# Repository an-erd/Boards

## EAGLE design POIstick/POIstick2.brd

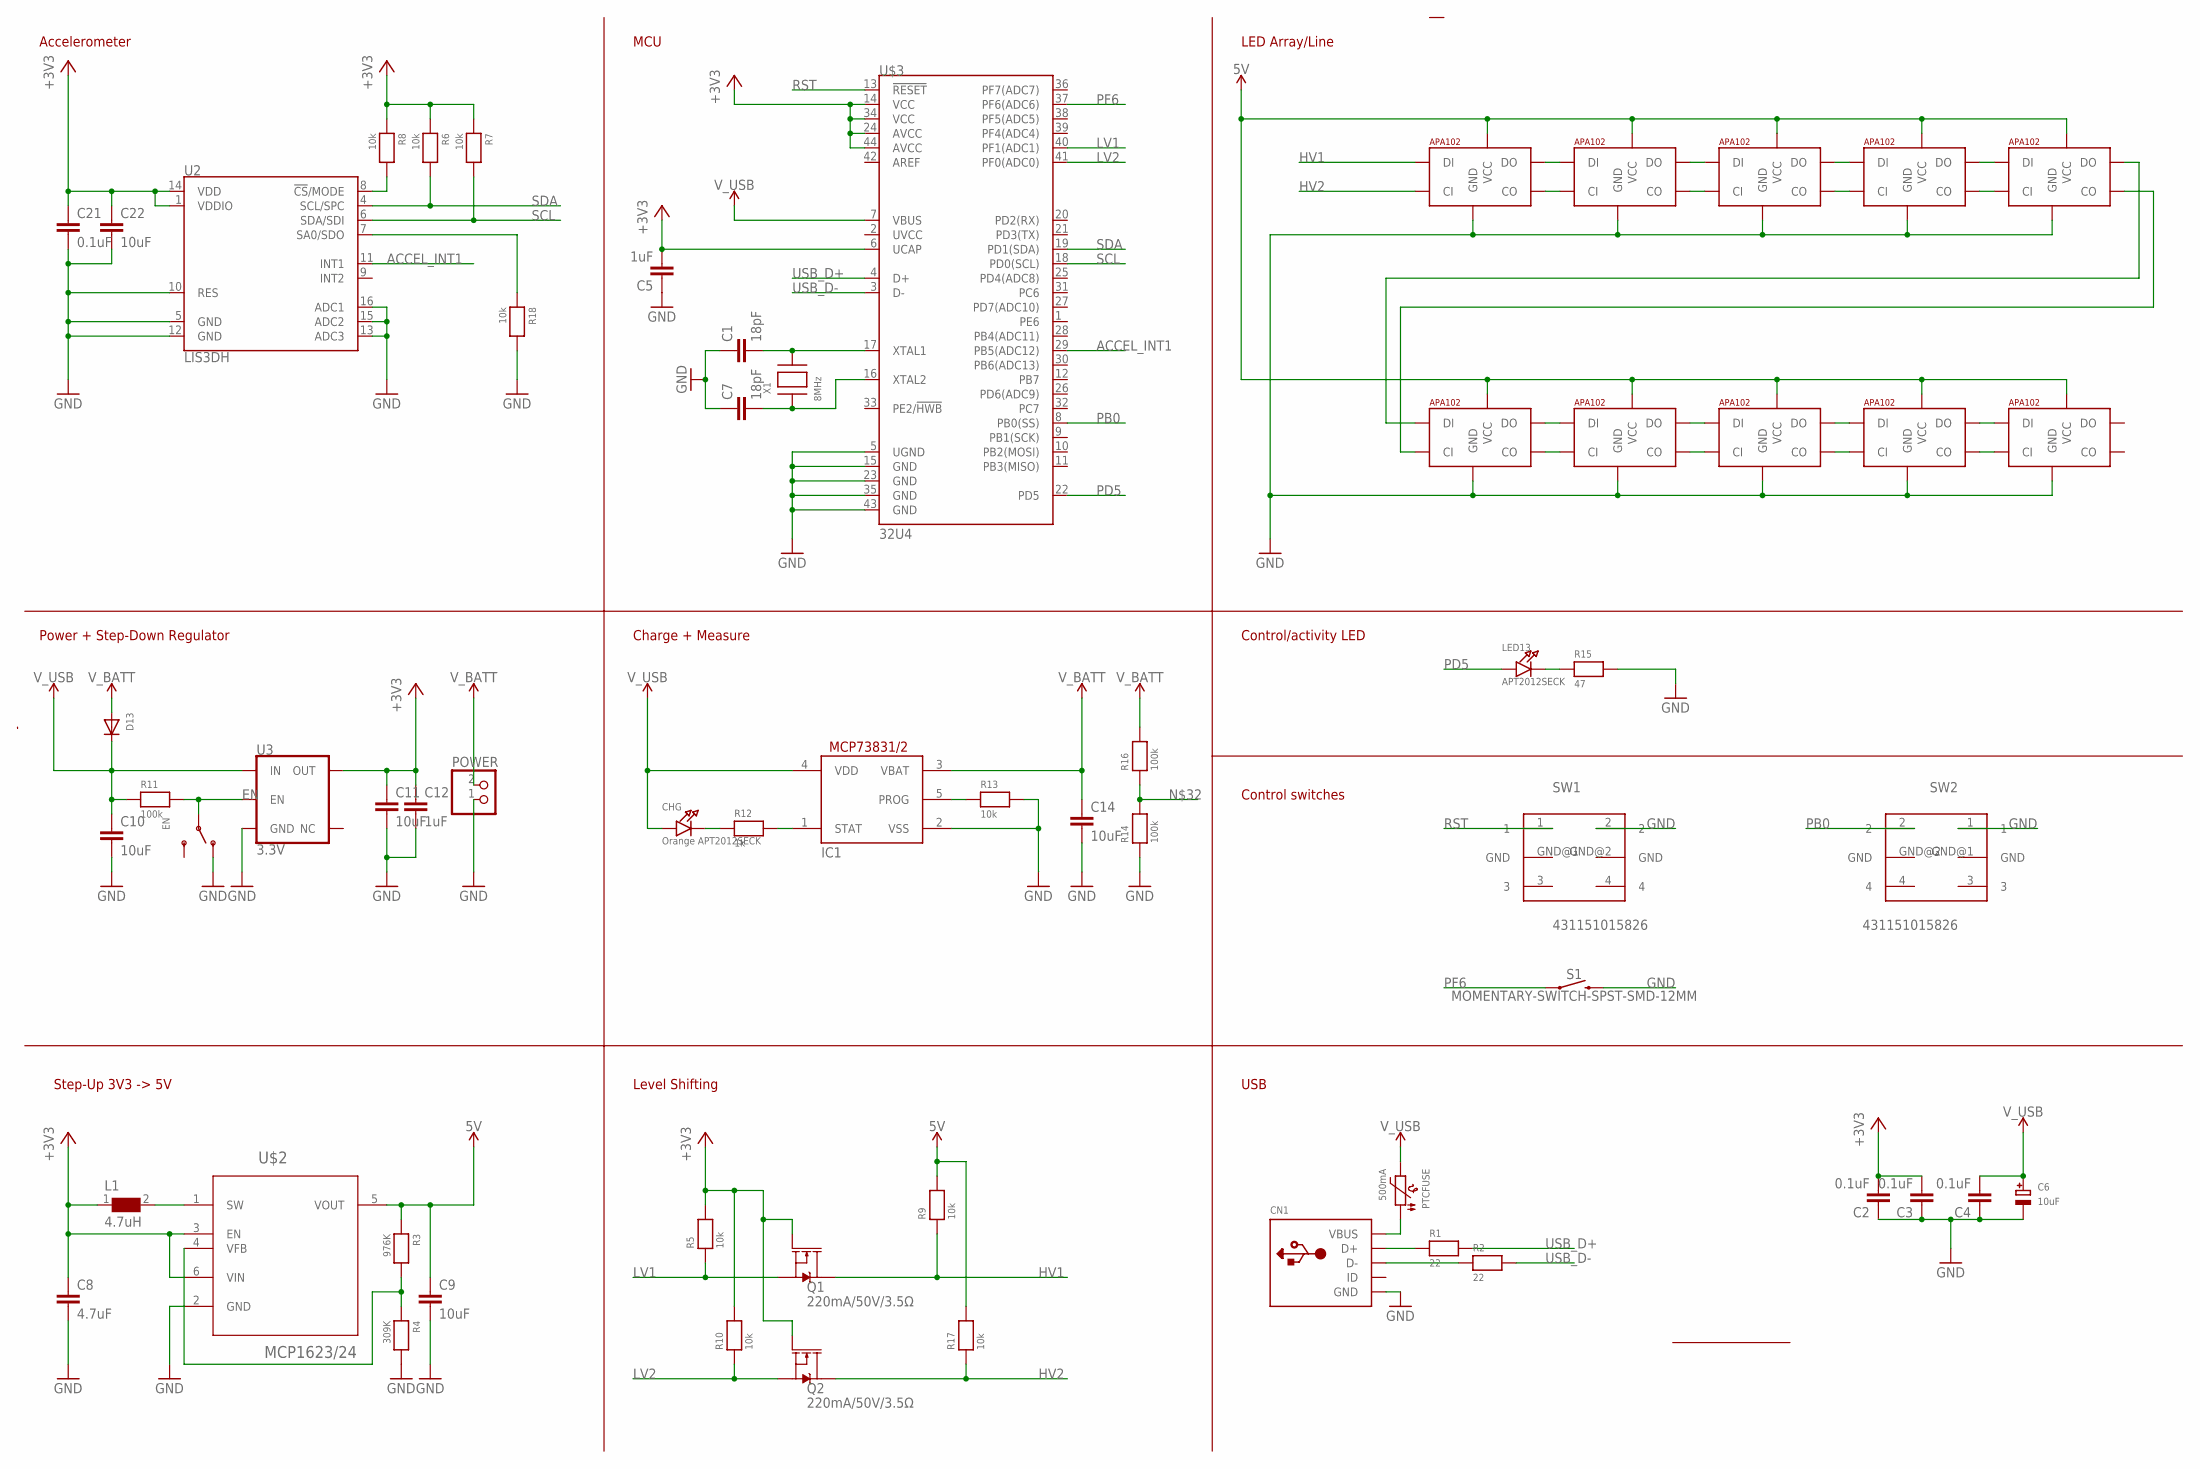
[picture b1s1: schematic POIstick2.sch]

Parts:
C1, C7: 18pF; C0603K
C2, C3, C4, C21: 0.1uF; C0603K
C5, C12: 1uF; C0603K
C6: 10uF; EIA3216-18/A-R
C8: 4.7uF; C0603K
C9, C10, C11, C14, C22: 10uF; C0603K
CHG: Orange APT2012SECK; CHIPLED_0603
CN1: USBMINIB; USB-MINIB
D13: DIODESOD-123; SOD-123
EN: SWITCH_SPDT; SPDT_SMT_SSSS811101
IC1: MCP73831/OT; SOT23-5L
L1: 4.7uH; WE-TPC_3816
LED13: APT2012SECK; CHIPLED_0603
POWER: JST_2PIN-THM; JST-PH-2-THM
PTCFUSE: 500mA; 1206
Q1, Q2: 220mA/50V/3.5Ω; SOT23-3
R1, R2: 22; 0603
R3: 976K; 0603
R4: 309K; 0603
R5, R6, R7, R8, R9, R10, R13, R17, R18: 10k; 0603
R11, R14, R16: 100k; 0603
R12: 1k; 0603
R15: 47; 0603
S1: MOMENTARY-SWITCH-SPST-SMD-12MM; TACTILE_SWITCH_SMD_12MM
SW1, SW2: 431151015826; 431181015816
U2: LIS3DH; LGA-16-3X3
U3: 3.3V; SOT23-5
U$2: MCP1623/24; SOT95P300X120-6N
U$3: 32U4; QFN-44
U$4, U$5, U$6, U$7, U$8, U$9, U$10, U$11, U$12, U$13: APA1025050; APA102_5050
X1: 8MHz; NX5032

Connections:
5V: C9.1, R3.1, R9.2, R17.2, U$2.5 (VOUT), U$4.1 (VCC), U$5.1 (VCC), U$6.1 (VCC), U$7.1 (VCC), U$8.1 (VCC), U$9.1 (VCC), U$10.1 (VCC), U$11.1 (VCC), U$12.1 (VCC), U$13.1 (VCC)
+3V3: C2.2, C3.2, C5.2, C8.1, C11.1, C12.1, C21.1, C22.1, L1.1, Q1.1 (G), Q2.1 (G), R5.2, R6.1, R7.1, R8.1, R10.2, U2.1 (VDDIO), U2.14 (VDD), U3.5 (OUT), U$2.3 (EN), U$2.6 (VIN), U$3.24 (AVCC), U$3.44 (AVCC)
ACCEL_INT1: U2.11 (INT1), U$3.29 (PB5(ADC12))
EN: EN.B, R11.2, U3.3 (EN)
GND: C1.1, C2.1, C3.1, C4.1, C5.1, C6.-, C7.1, C8.2, C9.2, C10.2, C11.2, C12.2, C14.2, C21.2, C22.2, CN1.GND, EN.A (O), IC1.2 (VSS), POWER.1 (2), R4.2, R13.2, R14.1, R15.2, R18.2, S1.3 (2), SW1.2, SW2.1, U2.5 (GND), U2.10 (RES), U2.12 (GND), U2.13 (ADC3), U2.15 (ADC2), U2.16 (ADC1), U3.2 (GND), U$2.2 (GND), U$4.6 (GND), U$5.6 (GND), U$6.6 (GND), U$7.6 (GND), U$8.6 (GND), U$9.6 (GND), U$10.6 (GND), U$11.6 (GND), U$12.6 (GND), U$13.6 (GND)
HV1: Q1.3 (D), R9.1, U$4.4 (DI)
HV2: Q2.3 (D), R17.1, U$4.5 (CI)
LV1: Q1.2 (S), R5.1, U$3.40 (PF1(ADC1))
LV2: Q2.2 (S), R10.1, U$3.41 (PF0(ADC0))
unnamed: CN1.D+, R1.1
unnamed: CN1.D-, R2.1
unnamed: R3.2, R4.1, U$2.4 (VFB)
unnamed: R18.1, U2.7 (SA0/SDO)
unnamed: CN1.VBUS, PTCFUSE.1
unnamed: C7.2, U$3.16 (XTAL2), X1.P$1
unnamed: C1.2, U$3.17 (XTAL1), X1.P$2
unnamed: U$4.3 (DO), U$5.4 (DI)
unnamed: U$4.2 (CO), U$5.5 (CI)
unnamed: U$5.3 (DO), U$6.4 (DI)
unnamed: U$5.2 (CO), U$6.5 (CI)
unnamed: U$6.3 (DO), U$7.4 (DI)
unnamed: U$6.2 (CO), U$7.5 (CI)
unnamed: U$7.3 (DO), U$8.4 (DI)
unnamed: U$7.2 (CO), U$8.5 (CI)
unnamed: U$8.3 (DO), U$9.4 (DI)
unnamed: U$8.2 (CO), U$9.5 (CI)
unnamed: R8.2, U2.8 (!CS!/MODE)
unnamed: L1.2, U$2.1 (SW)
unnamed: U$9.3 (DO), U$10.4 (DI)
unnamed: U$9.2 (CO), U$10.5 (CI)
unnamed: U$10.2 (CO), U$11.5 (CI)
unnamed: U$10.3 (DO), U$11.4 (DI)
unnamed: IC1.1 (STAT), R12.2
unnamed: U$11.3 (DO), U$12.4 (DI)
unnamed: CHG.C, R12.1
unnamed: U$11.2 (CO), U$12.5 (CI)
unnamed: IC1.5 (PROG), R13.1
unnamed: U$12.2 (CO), U$13.5 (CI)
unnamed: LED13.C, R14.2, R15.1, R16.1
unnamed: U$12.3 (DO), U$13.4 (DI)
PB0: SW2.2, U$3.8 (PB0(SS))
PD5: LED13.A, U$3.22 (PD5)
PF6: S1.1, U$3.37 (PF6(ADC6))
RST: SW1.1, U$3.13 (!RESET)
SCL: R7.2, U2.6 (SDA/SDI), U$3.18 (PD0(SCL))
SDA: R6.2, U2.4 (SCL/SPC), U$3.19 (PD1(SDA))
USB_D+: R1.2, U$3.4 (D+)
USB_D-: R2.2, U$3.3 (D-)
V_BATT: C14.1, D13.A, IC1.3 (VBAT), POWER.2 (1), R16.2
V_USB: C4.2, C6.+, C10.1, CHG.A, D13.C, IC1.4 (VDD), PTCFUSE.2, R11.1, U3.1 (IN), U$3.7 (VBUS)

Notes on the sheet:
LED Array/Line
Control/activity LED
Step-Up 3V3 -> 5V
Control switches
MCU
USB
Accelerometer
Power + Step-Down Regulator
Charge + Measure
Level Shifting

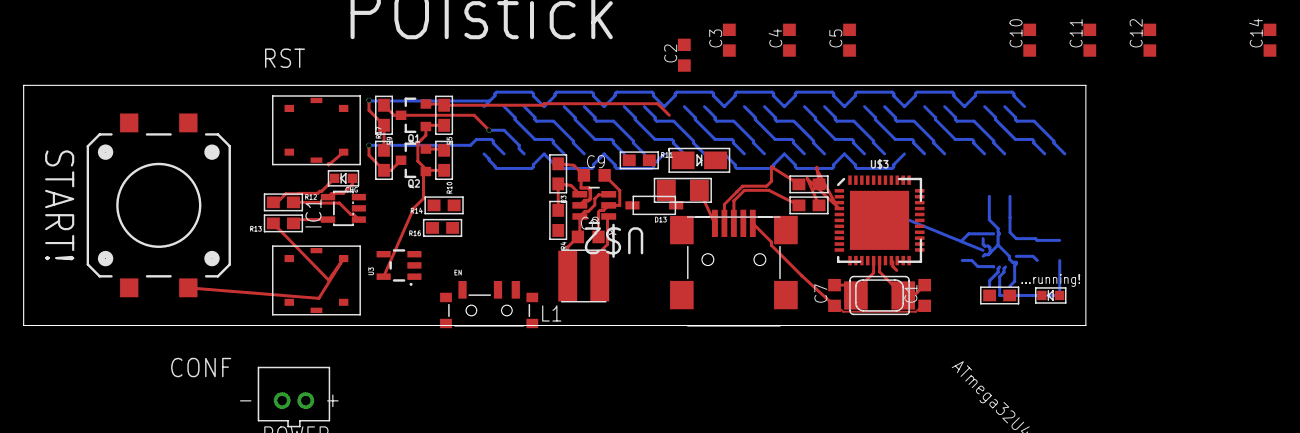
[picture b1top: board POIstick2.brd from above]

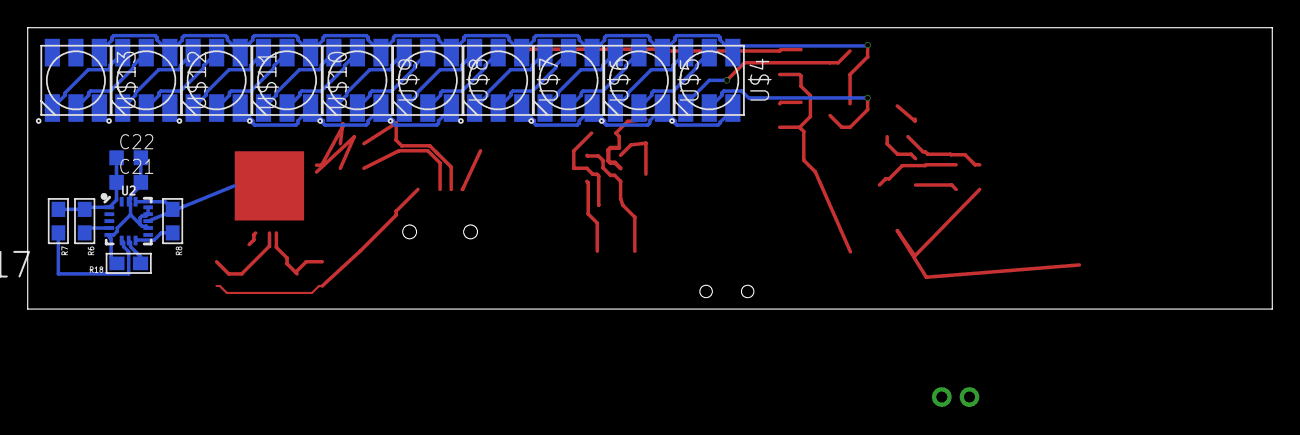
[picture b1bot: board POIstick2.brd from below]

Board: 2 copper layers, 89.8 x 20.3 mm, 62 parts (17 on the bottom side), 50 nets.

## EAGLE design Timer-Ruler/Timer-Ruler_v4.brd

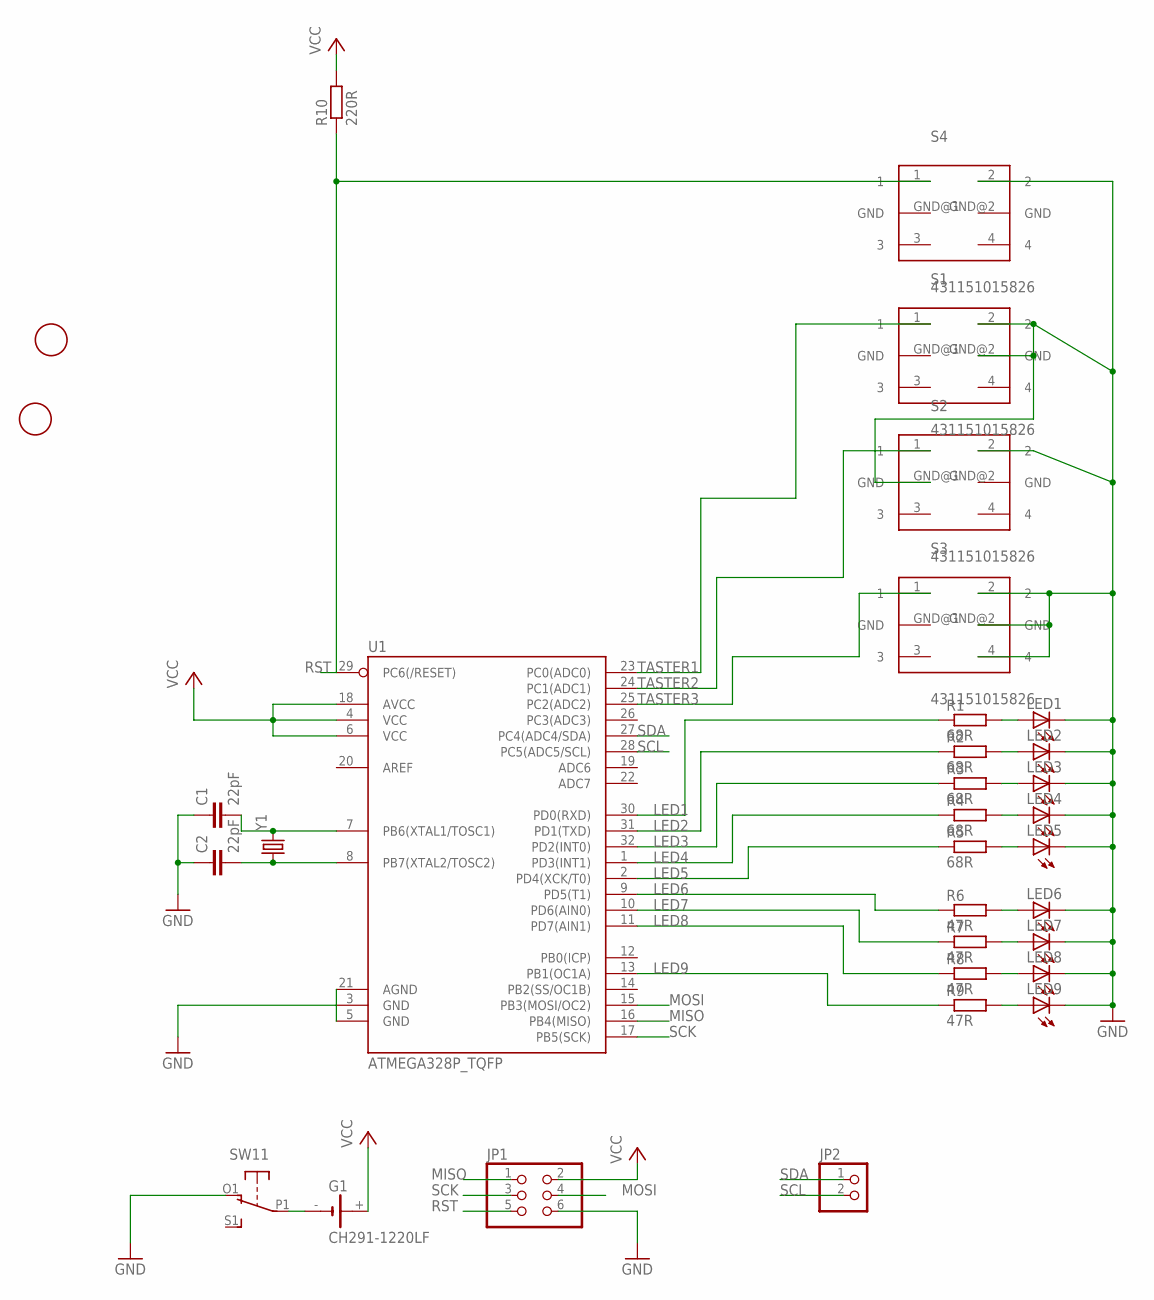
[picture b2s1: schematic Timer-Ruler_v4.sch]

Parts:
C1, C2: 22pF; C0603
G1: CH291-1220LF
JP1: PINHD-2X3; 2X03
JP2: PINHD-1X2; 1X02
LED1, LED2, LED3, LED4, LED5, LED6, LED7, LED8, LED9: LEDCHIP-LED0603; CHIP-LED0603
R1, R2, R3, R4, R5: 68R; R0603
R6, R7, R8, R9: 47R; R0603
R10: 220R; R0603
S1, S2, S3, S4: 431151015826; 431181015816
SW1: DPDT-EG1390; EG1390
U1: ATMEGA328P_TQFP; TQFP32-08
U$1, U$2: FIDUCIAL; FIDUCIAL_1MM
Y1: CRYSTALCRYSTAL-SMD-5X3-12.288MHZ; CRYSTAL-SMD-5X3

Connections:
GND: C1.1, C2.1, JP1.6, LED1.C, LED2.C, LED3.C, LED4.C, LED5.C, LED6.C, LED7.C, LED8.C, LED9.C, S1.2, S1.GND@2 (GND), S2.2, S2.GND@1 (GND), S3.2, S3.4, S3.GND@2 (GND), S4.2, SW1.O1 (O), U1.3 (GND)
LED1: R1.1, U1.30 (PD0(RXD))
LED2: R2.1, U1.31 (PD1(TXD))
LED3: R3.1, U1.32 (PD2(INT0))
LED4: R4.1, U1.1 (PD3(INT1))
LED5: R5.1, U1.2 (PD4(XCK/T0))
LED6: R6.1, U1.9 (PD5(T1))
LED7: R7.1, U1.10 (PD6(AIN0))
LED8: R8.1, U1.11 (PD7(AIN1))
LED9: R9.1, U1.13 (PB1(OC1A))
MISO: JP1.1, U1.16 (PB4(MISO))
MOSI: JP1.4, U1.15 (PB3(MOSI/OC2))
unnamed: LED1.A, R1.2
unnamed: LED2.A, R2.2
unnamed: LED3.A, R3.2
unnamed: LED4.A, R4.2
unnamed: LED5.A, R5.2
unnamed: LED6.A, R6.2
unnamed: LED7.A, R7.2
unnamed: LED8.A, R8.2
unnamed: LED9.A, R9.2
unnamed: C1.2, U1.7 (PB6(XTAL1/TOSC1)), Y1.3 (2)
unnamed: C2.2, U1.8 (PB7(XTAL2/TOSC2)), Y1.1
unnamed: U1.5 (GND), U1.21 (AGND)
unnamed: G1.-, SW1.P1
RST: JP1.5, R10.1, S4.1, U1.29 (PC6(/RESET))
SCK: JP1.3, U1.17 (PB5(SCK))
SCL: JP2.2, U1.28 (PC5(ADC5/SCL))
SDA: JP2.1, U1.27 (PC4(ADC4/SDA))
TASTER1: S1.1, U1.23 (PC0(ADC0))
TASTER2: S2.1, U1.24 (PC1(ADC1))
TASTER3: S3.1, U1.25 (PC2(ADC2))
VCC: G1.+, JP1.2, R10.2, U1.4 (VCC), U1.6 (VCC), U1.18 (AVCC)

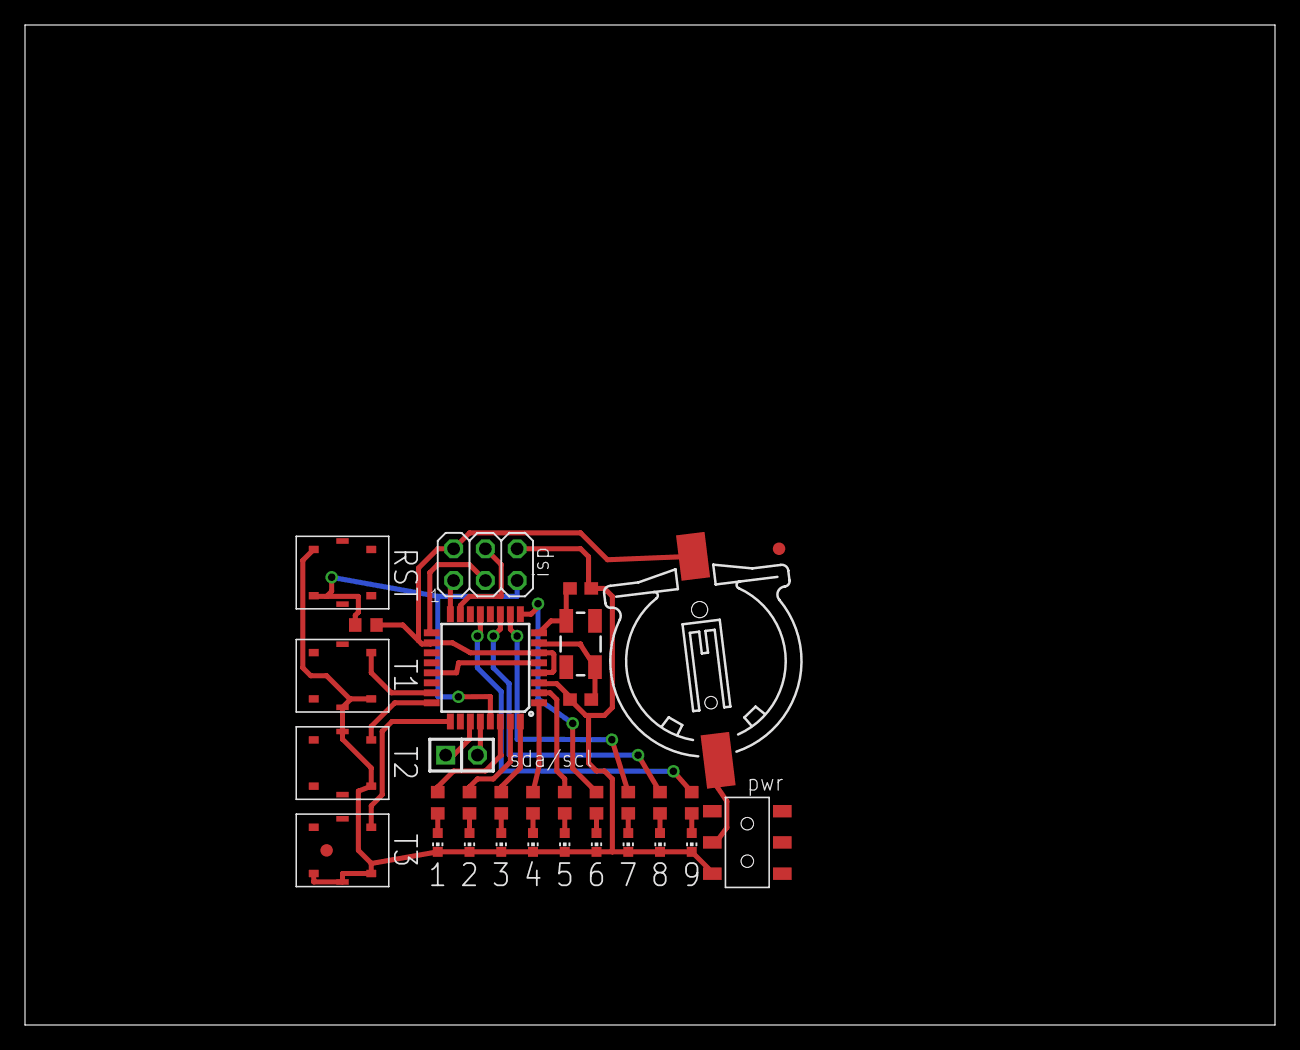
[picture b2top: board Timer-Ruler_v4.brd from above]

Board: 2 copper layers, 100.0 x 80.0 mm, 33 parts (0 on the bottom side), 33 nets.

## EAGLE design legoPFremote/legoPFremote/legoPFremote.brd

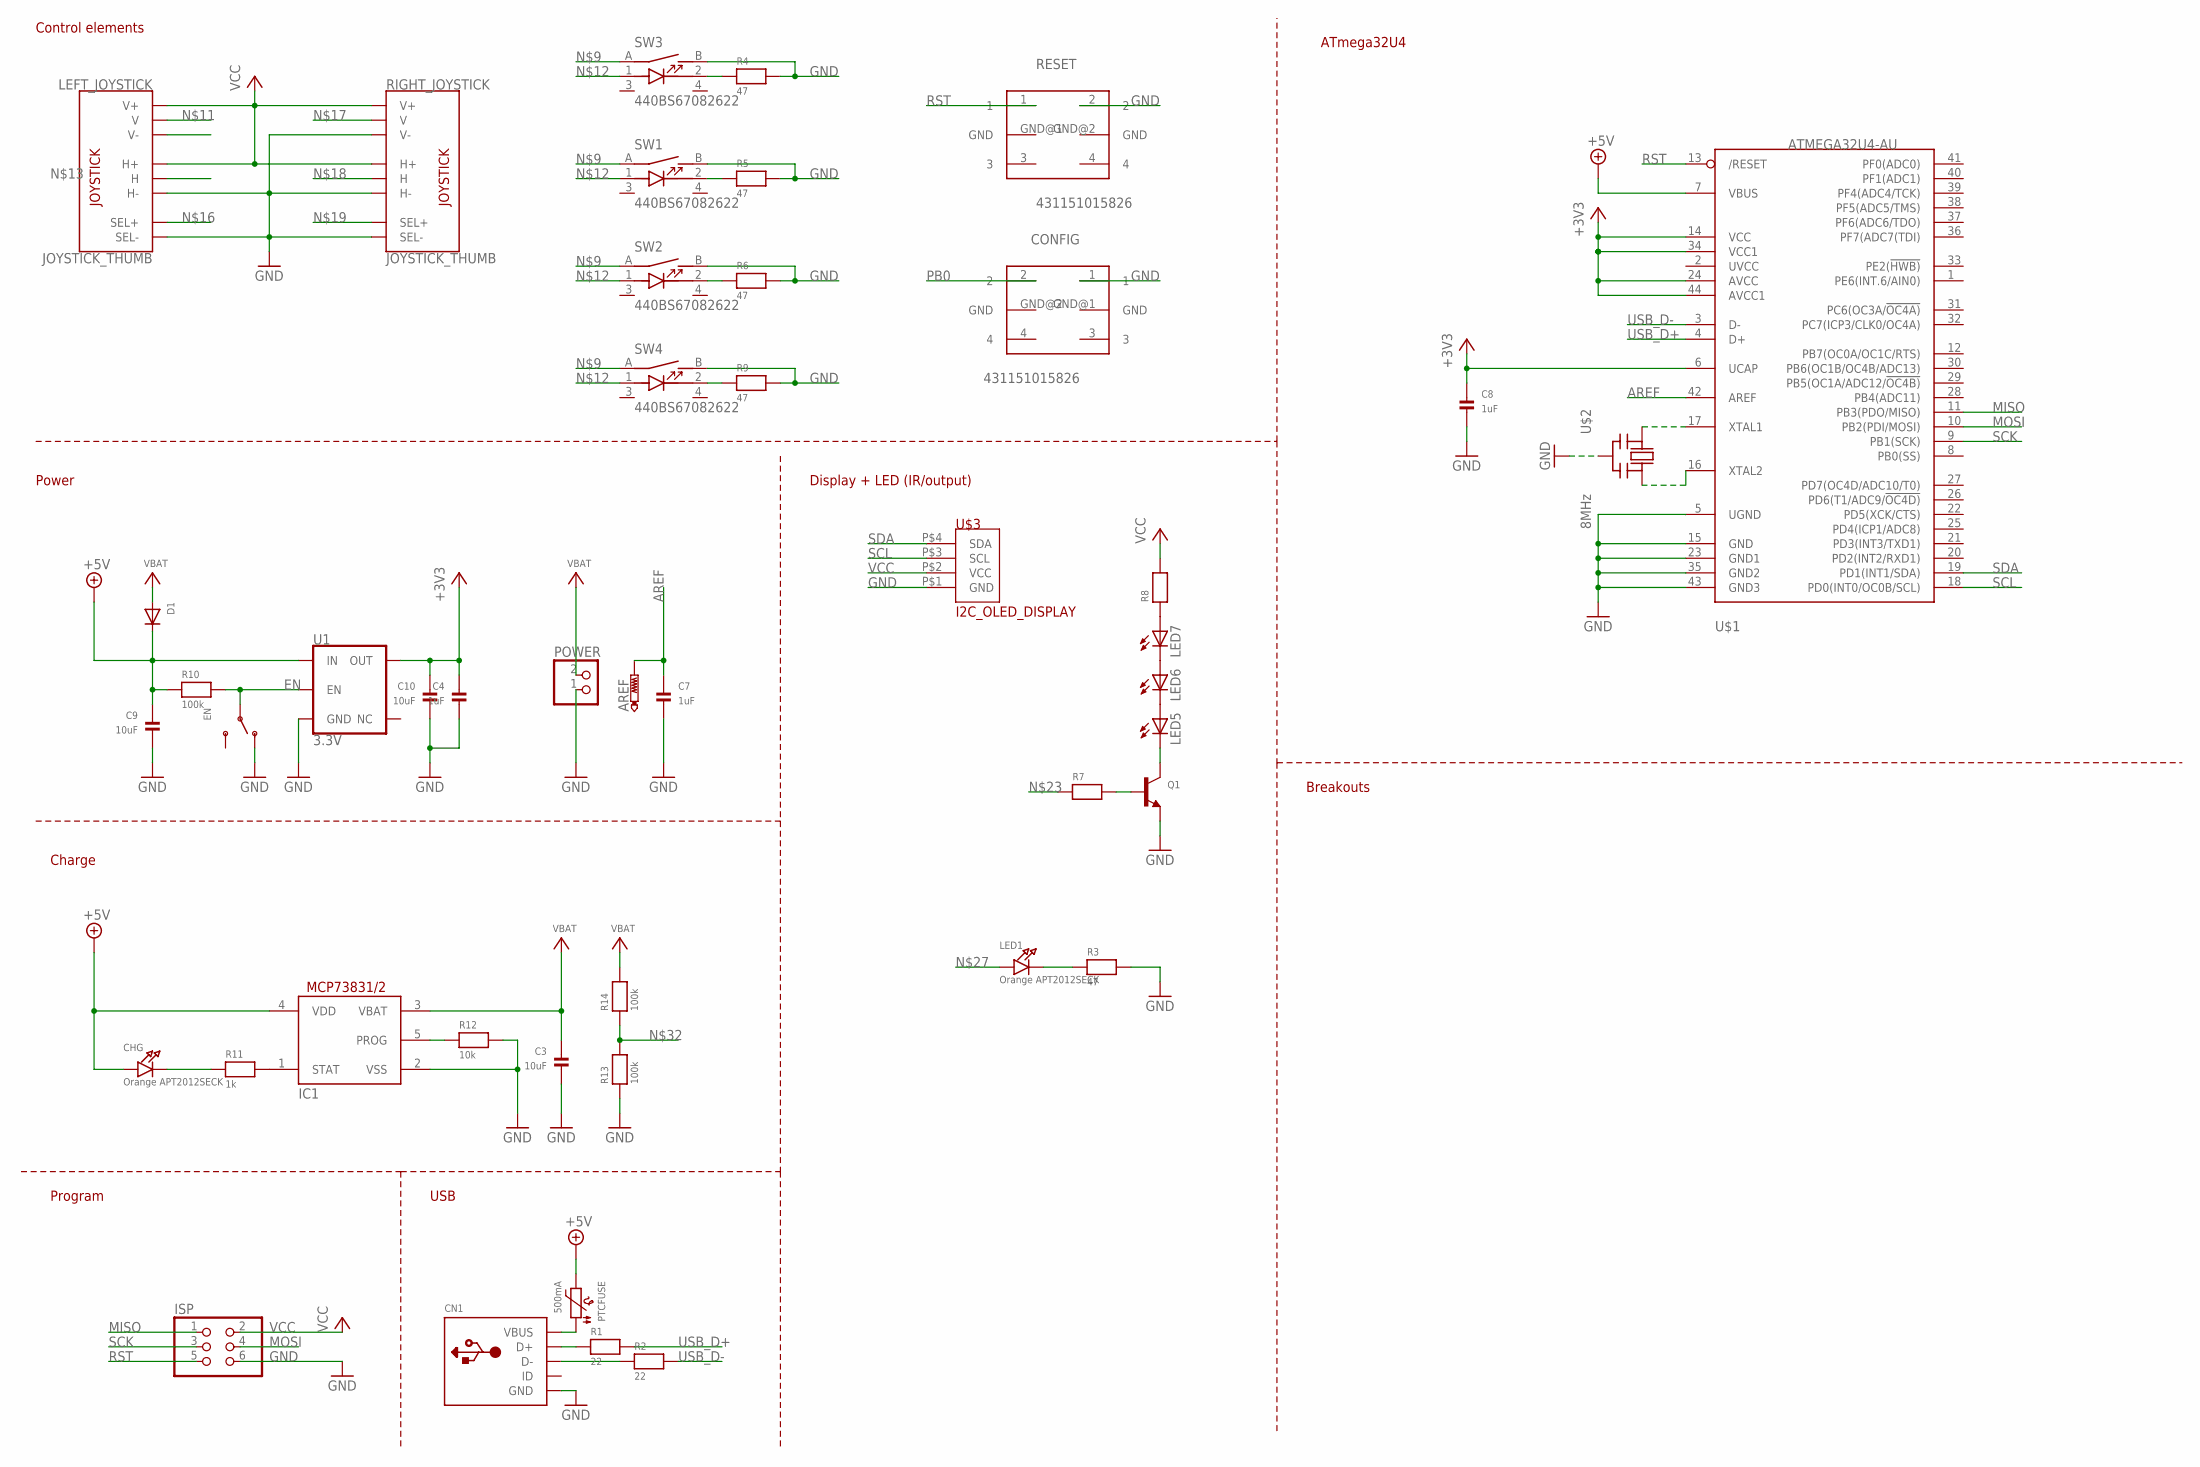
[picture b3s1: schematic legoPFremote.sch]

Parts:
AREF: PTR1B1,27; B1,27
C3, C9, C10: 10uF; 0805
C4, C7, C8: 1uF; 0805
CHG: Orange APT2012SECK; CHIPLED_0805
CN1: USBMINIB; USB-MINIB
CONFIG: 431151015826; 431181015816
D1: DIODESOD-123; SOD-123
EN: SWITCH_SPDT; SPDT_SMT_SSSS811101
IC1: MCP73831/OT; SOT23-5L
ISP: PINHD-2X3; 2X03
LED1: Orange APT2012SECK; CHIPLED_0805
LED5, LED6, LED7: LEDIRL80A; IRL80A
LEFT_JOYSTICK: JOYSTICK_THUMB; JOYSTICK
POWER: JST_2PIN-THM; JST-PH-2-THM
PTCFUSE: 500mA; 1206
Q1: TRANSISTOR_NPN; SOT23-R
R1, R2: 22; 0805
R3, R4, R5, R6, R9: 47; 0805
R7, R8: RESISTOR0805; 0805
R10, R13, R14: 100k; 0805
R11: 1k; 0805
R12: 10k; 0805
RESET: 431151015826; 431181015816
RIGHT_JOYSTICK: JOYSTICK_THUMB; JOYSTICK
SW1, SW2, SW3, SW4: 440BS67082622
U1: 3.3V; SOT23-5
U$1: ATMEGA32U4-AU; TQFP44
U$2: 8MHz; CSTCR-G
U$3: I2C_OLED_DISPLAY; HD1X4

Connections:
+3V3: C4.1, C8.1, C10.1, U1.5 (OUT), U$1.6 (UCAP), U$1.14 (VCC), U$1.24 (AVCC), U$1.34 (VCC1), U$1.44 (AVCC1)
+5V: C9.1, CHG.A, D1.C, IC1.4 (VDD), PTCFUSE.2, R10.1, U1.1 (IN), U$1.7 (VBUS)
AREF: AREF.TP, C7.1, U$1.42 (AREF)
EN: EN.B, R10.2, U1.3 (EN)
GND: C3.2, C4.2, C7.2, C8.2, C9.2, C10.2, CN1.GND, CONFIG.1, EN.A (O), IC1.2 (VSS), ISP.6, LEFT_JOYSTICK.B2A (SEL-), LEFT_JOYSTICK.H3 (H-), POWER.1 (2), Q1.2 (E), R3.2, R4.2, R5.2, R6.2, R9.2, R12.2, R13.1, RESET.2, RIGHT_JOYSTICK.B2A (SEL-), RIGHT_JOYSTICK.H3 (H-), RIGHT_JOYSTICK.V3 (V-), SW1.B, SW2.B, SW3.B, SW4.B, U1.2 (GND), U$1.5 (UGND), U$1.15 (GND), U$1.23 (GND1), U$1.35 (GND2), U$1.43 (GND3), U$2.2 (GND), U$3.P$1 (GND)
MISO: ISP.1, U$1.11 (PB3(PDO/MISO))
MOSI: ISP.4, U$1.10 (PB2(PDI/MOSI))
unnamed: CN1.D+, R1.1
unnamed: CN1.D-, R2.1
unnamed: LED5.A, LED6.K (C)
unnamed: LED6.A, LED7.K (C)
unnamed: CN1.VBUS, PTCFUSE.1
unnamed: U$1.16 (XTAL2), U$2.3 (OUT)
unnamed: U$1.17 (XTAL1), U$2.1 (IN)
unnamed: LED1.C, R3.1
unnamed: SW1.A, SW2.A, SW3.A, SW4.A
unnamed: R4.1, SW3.2
unnamed: SW1.1, SW2.1, SW3.1, SW4.1
unnamed: R5.1, SW1.2
unnamed: R6.1, SW2.2
unnamed: Q1.1 (B), R7.2
unnamed: LED7.A, R8.1
unnamed: LED5.K (C), Q1.3 (C)
unnamed: R9.1, SW4.2
unnamed: IC1.1 (STAT), R11.2
unnamed: CHG.C, R11.1
unnamed: IC1.5 (PROG), R12.1
unnamed: R13.2, R14.1
PB0: CONFIG.2
RST: ISP.5, RESET.1, U$1.13 (/RESET)
SCK: ISP.3, U$1.9 (PB1(SCK))
SCL: U$1.18 (PD0(INT0/OC0B/SCL)), U$3.P$3 (SCL)
SDA: U$1.19 (PD1(INT1/SDA)), U$3.P$4 (SDA)
USB_D+: R1.2, U$1.4 (D+)
USB_D-: R2.2, U$1.3 (D-)
VBAT: C3.1, D1.A, IC1.3 (VBAT), POWER.2 (1), R14.2
VCC: ISP.2, LEFT_JOYSTICK.H1 (H+), LEFT_JOYSTICK.V1 (V+), R8.2, RIGHT_JOYSTICK.H1 (H+), RIGHT_JOYSTICK.V1 (V+), U$3.P$2 (VCC)

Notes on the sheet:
Control elements
Power
Charge
Program
Breakouts
Display + LED (IR/output)
ATmega32U4
USB

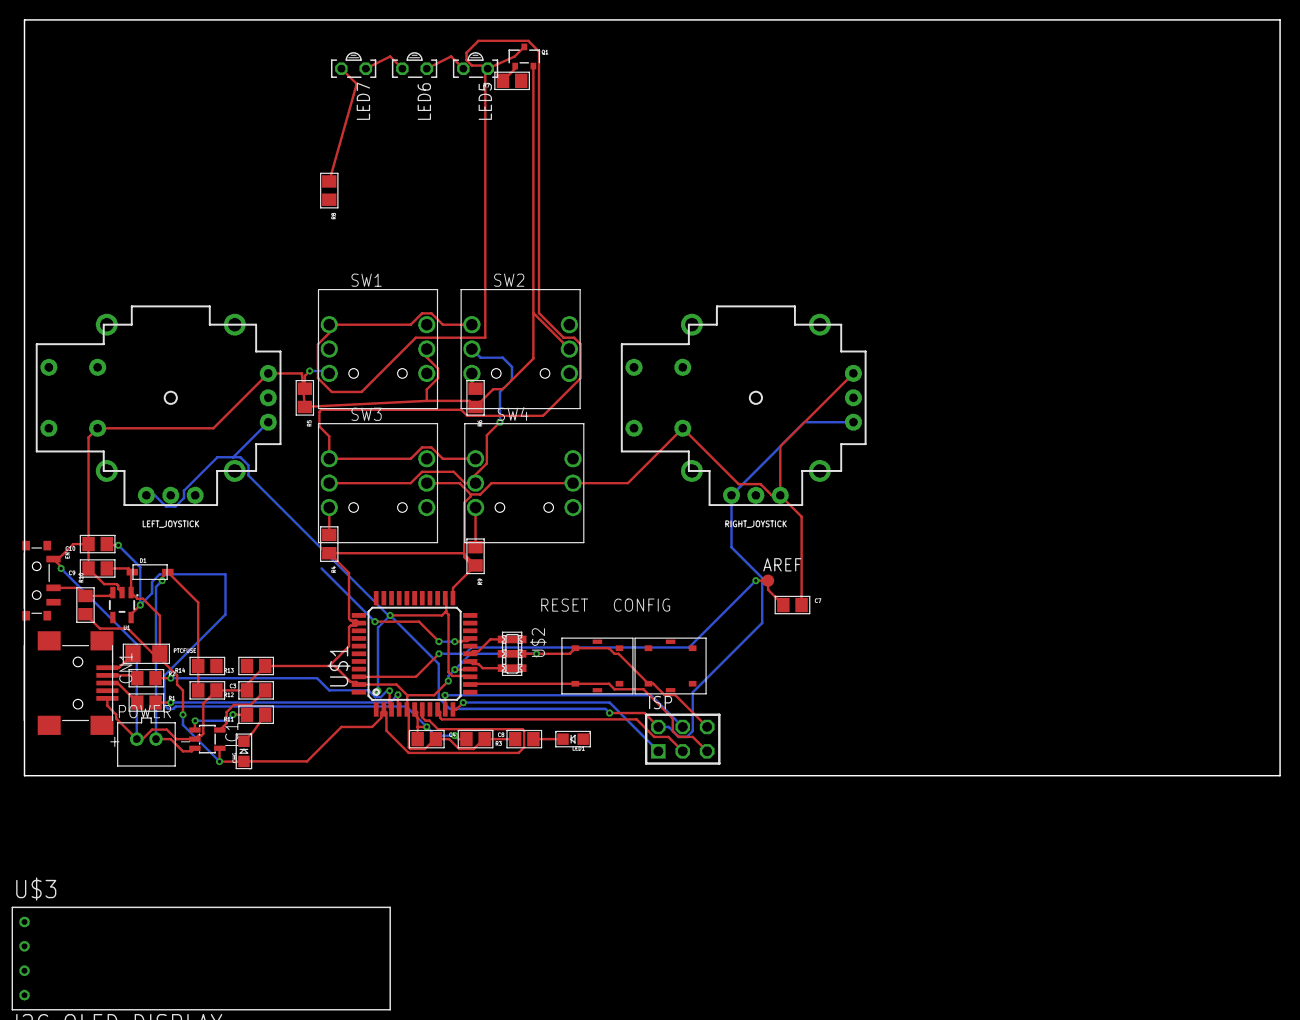
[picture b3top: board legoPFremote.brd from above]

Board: 2 copper layers, 130.8 x 78.7 mm, 46 parts (0 on the bottom side), 36 nets.

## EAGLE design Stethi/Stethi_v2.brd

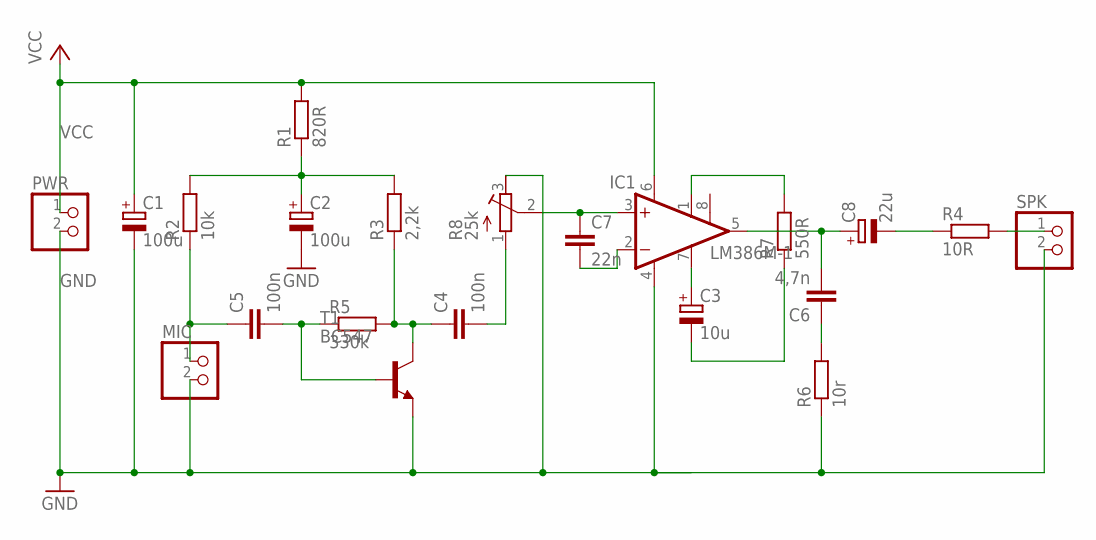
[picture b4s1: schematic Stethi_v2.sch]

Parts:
C1, C2: 100u; D/7343-31R
C3: 10u; A/3216-18R
C4, C5: 100n; C0805K
C6: 4,7n; C0805K
C7: 22n; C0805K
C8: 22u; A/3216-18R
IC1: LM386M-1; SO08
MIC: PINHD-1X2; 1X02
PWR: PINHD-1X2; 1X02
R1: 820R; R0805
R2: 10k; R0805
R3: 2,2k; R0805
R4: 10R; R0805
R5: 330k; R0805
R6: 10r; R0805
R7: 550R; R0805
R8: 25k; RTRIM5X
SPK: PINHD-1X2; 1X02
T1: BC547; SOT23

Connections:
GND: C1.-, C2.-, IC1.4 (GND), MIC.2, PWR.2, R6.1, R8.3 (E), SPK.2, T1.2 (E)
unnamed: C2.+, R1.1, R2.2, R3.2
unnamed: C5.1, MIC.1, R2.1
unnamed: C7.2, IC1.2 (-IN)
unnamed: C7.1, IC1.3 (+IN), R8.2 (S)
unnamed: C5.2, R5.1, T1.1 (B)
unnamed: C4.2, R8.1 (A)
unnamed: C4.1, R3.1, R5.2, T1.3 (C)
unnamed: C6.1, R6.2
unnamed: C3.+, IC1.7 (BYPASS)
unnamed: R4.2, SPK.1
unnamed: C6.2, C8.+, IC1.5 (OUT)
unnamed: C8.-, R4.1
unnamed: IC1.1 (GAIN), R7.2
unnamed: C3.-, R7.1
VCC: C1.+, IC1.6 (VS), PWR.1, R1.2

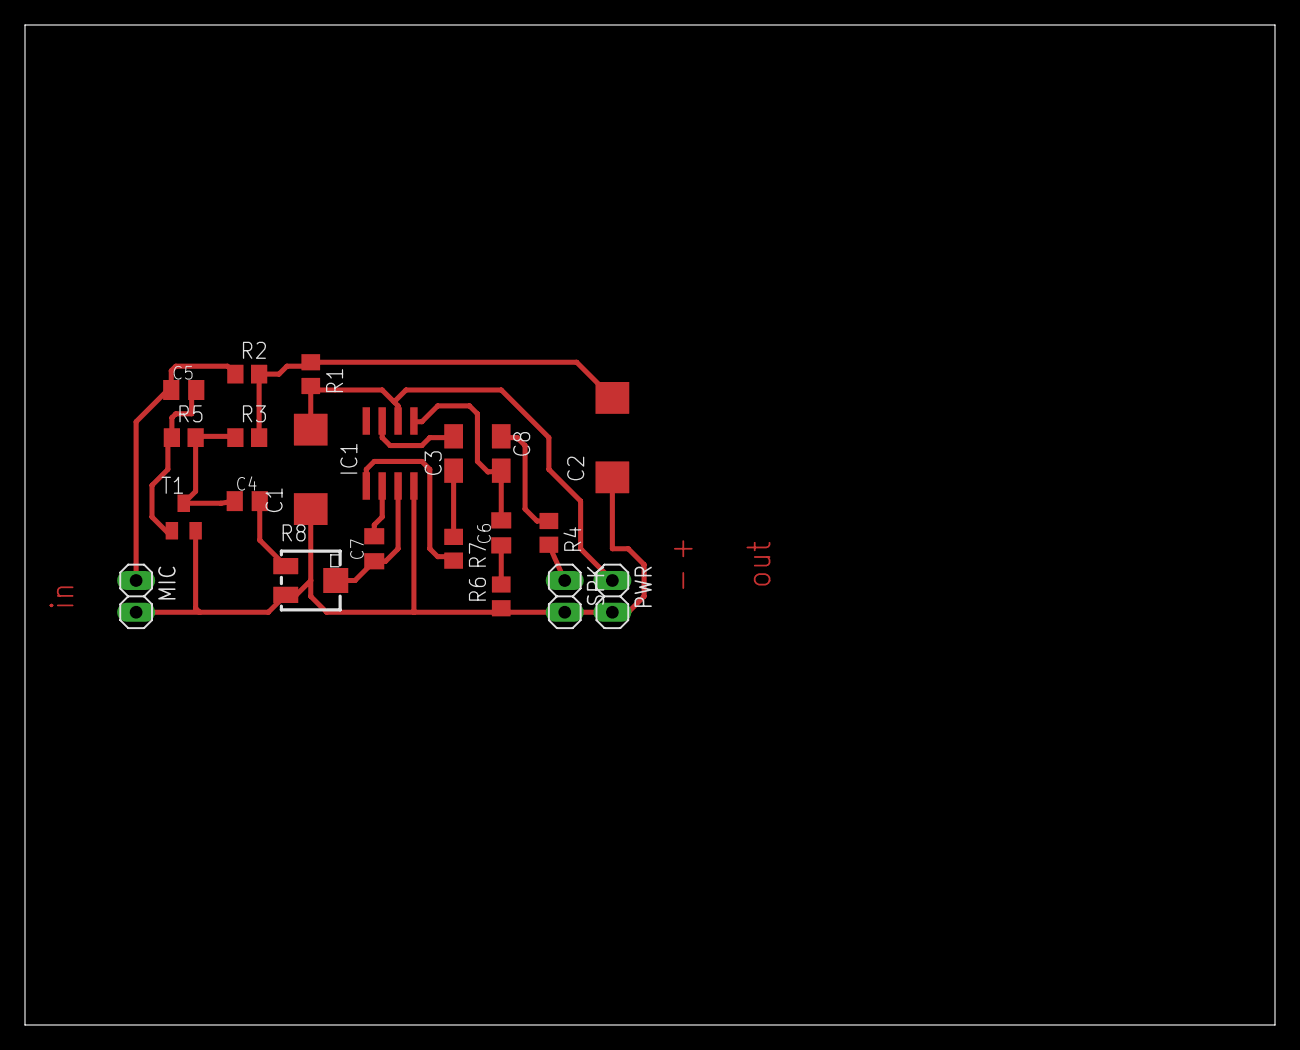
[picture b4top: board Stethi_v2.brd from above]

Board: 2 copper layers, 100.0 x 80.0 mm, 21 parts (0 on the bottom side), 16 nets.

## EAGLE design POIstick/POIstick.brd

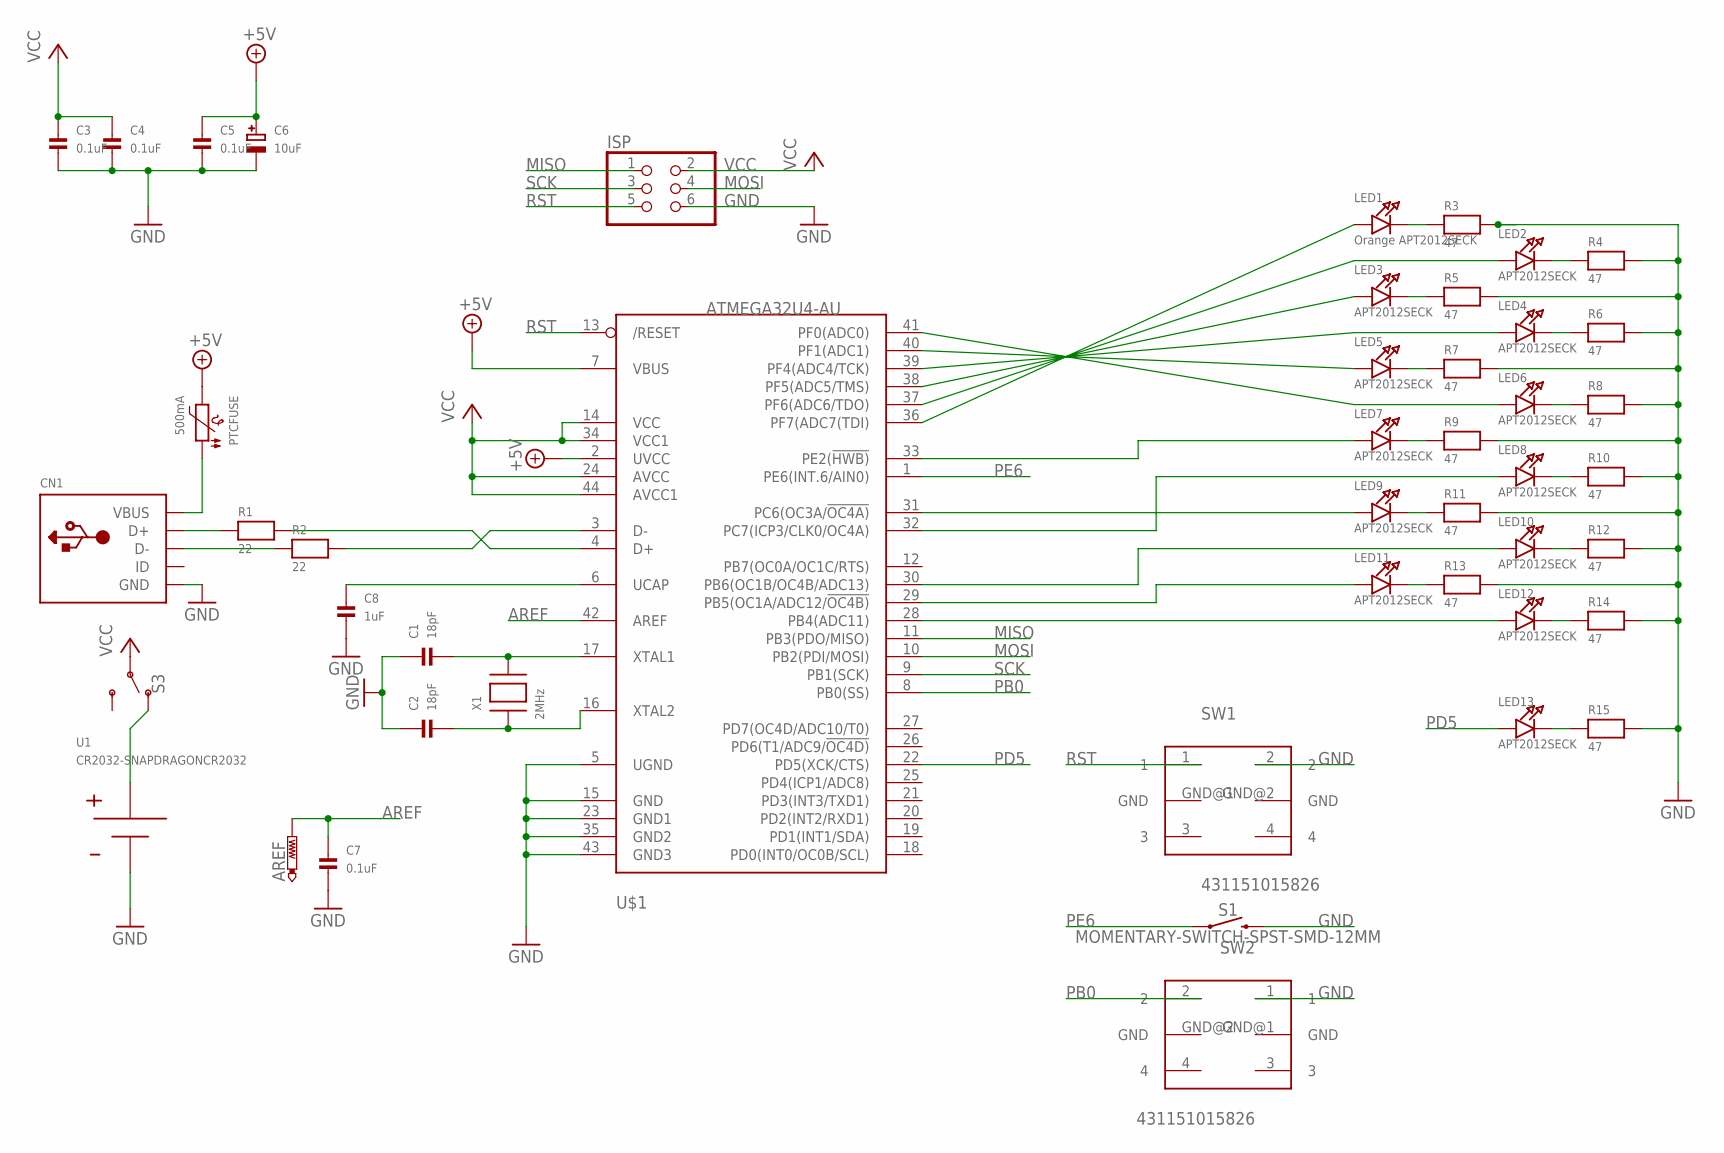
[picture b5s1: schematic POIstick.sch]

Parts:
AREF: PTR1B1,27; B1,27
C1, C2: 18pF; 0805
C3, C4, C5, C7: 0.1uF; 0805
C6: 10uF; EIA3216-18/A-W
C8: 1uF; 0805
CN1: USBMINIB; USB-MINIB
ISP: PINHD-2X3; 2X03
LED1: Orange APT2012SECK; CHIPLED_0805
LED2, LED3, LED4, LED5, LED6, LED7, LED8, LED9, LED10, LED11, LED12, LED13: APT2012SECK; CHIPLED_0805
PTCFUSE: 500mA; 1206
R1, R2: 22; 0805
R3, R4, R5, R6, R7, R8, R9, R10, R11, R12, R13, R14, R15: 47; 0805
S1: MOMENTARY-SWITCH-SPST-SMD-12MM; TACTILE_SWITCH_SMD_12MM
S3: SWITCH-SPDT-SMD-RIGHT-ANGLE; SWITCH_SPST_SMD_A
SW1, SW2: 431151015826; 431181015816
U1: CR2032-SNAPDRAGONCR2032; CR2032-SNAPDRAGON
U$1: ATMEGA32U4-AU; TQFP44
X1: 2MHz; NX5032

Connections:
+5V: C5.1, C6.+, PTCFUSE.2, U$1.2 (UVCC), U$1.7 (VBUS)
AREF: AREF.TP, C7.1, U$1.42 (AREF)
GND: C1.1, C2.1, C3.2, C4.2, C5.2, C6.-, C7.2, C8.2, CN1.GND, ISP.6, R3.2, R4.2, R5.2, R6.2, R7.2, R8.2, R9.2, R10.2, R11.2, R12.2, R13.2, R14.2, R15.2, S1.3 (2), SW1.2, SW2.1, U1.V-, U$1.5 (UGND), U$1.15 (GND), U$1.23 (GND1), U$1.35 (GND2), U$1.43 (GND3)
MISO: ISP.1, U$1.11 (PB3(PDO/MISO))
MOSI: ISP.4, U$1.10 (PB2(PDI/MOSI))
unnamed: CN1.D+, R1.1
unnamed: CN1.D-, R2.1
unnamed: R1.2, U$1.4 (D+)
unnamed: R2.2, U$1.3 (D-)
unnamed: CN1.VBUS, PTCFUSE.1
unnamed: C2.2, U$1.16 (XTAL2), X1.P$1
unnamed: C1.2, U$1.17 (XTAL1), X1.P$2
unnamed: LED1.C, R3.1
unnamed: LED2.A, U$1.37 (PF6(ADC6/TDO))
unnamed: LED2.C, R4.1
unnamed: LED1.A, U$1.36 (PF7(ADC7(TDI))
unnamed: LED3.C, R5.1
unnamed: LED3.A, U$1.38 (PF5(ADC5/TMS))
unnamed: LED4.C, R6.1
unnamed: LED4.A, U$1.39 (PF4(ADC4/TCK))
unnamed: LED5.C, R7.1
unnamed: LED5.A, U$1.40 (PF1(ADC1))
unnamed: LED6.C, R8.1
unnamed: LED6.A, U$1.41 (PF0(ADC0))
unnamed: LED7.C, R9.1
unnamed: LED7.A, U$1.33 (PE2(!HWB))
unnamed: LED8.C, R10.1
unnamed: LED8.A, U$1.32 (PC7(ICP3/CLK0/OC4A))
unnamed: LED9.C, R11.1
unnamed: LED9.A, U$1.31 (PC6(OC3A/!OC4A))
unnamed: LED10.C, R12.1
unnamed: LED10.A, U$1.30 (PB6(OC1B/OC4B/ADC13))
unnamed: LED11.C, R13.1
unnamed: LED11.A, U$1.29 (PB5(OC1A/ADC12/!OC4B))
unnamed: LED12.C, R14.1
unnamed: LED12.A, U$1.28 (PB4(ADC11))
unnamed: LED13.C, R15.1
unnamed: S3.1 (O), U1.V+
unnamed: C8.1, U$1.6 (UCAP)
PB0: SW2.2, U$1.8 (PB0(SS))
PD5: LED13.A, U$1.22 (PD5(XCK/CTS))
PE6: S1.1, U$1.1 (PE6(INT.6/AIN0))
RST: ISP.5, SW1.1, U$1.13 (/RESET)
SCK: ISP.3, U$1.9 (PB1(SCK))
VCC: C3.1, C4.1, ISP.2, S3.2, U$1.14 (VCC), U$1.24 (AVCC), U$1.34 (VCC1), U$1.44 (AVCC1)

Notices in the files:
parts and their libraries:
Wurth_Elektronik_Electromechanic_Switchs: Copyright: Würth Elektronik
SparkFun-Switches: Licensing: Creative Commons ShareAlike 4.0 International - https://creativecommons.org/licenses/by-sa/4.0
